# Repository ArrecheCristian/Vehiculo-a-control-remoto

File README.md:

# Vehiculo a control remoto
* Integración de Hardware y Software. 
* Diseño y desarrollo de PCB.
* Integración de componentes de hardware. 
* Manejo y medición de sensor de proximidad.
* Control inalámbrico (vía Bluetooth).
* Batería.
* Lenguaje de programación C.

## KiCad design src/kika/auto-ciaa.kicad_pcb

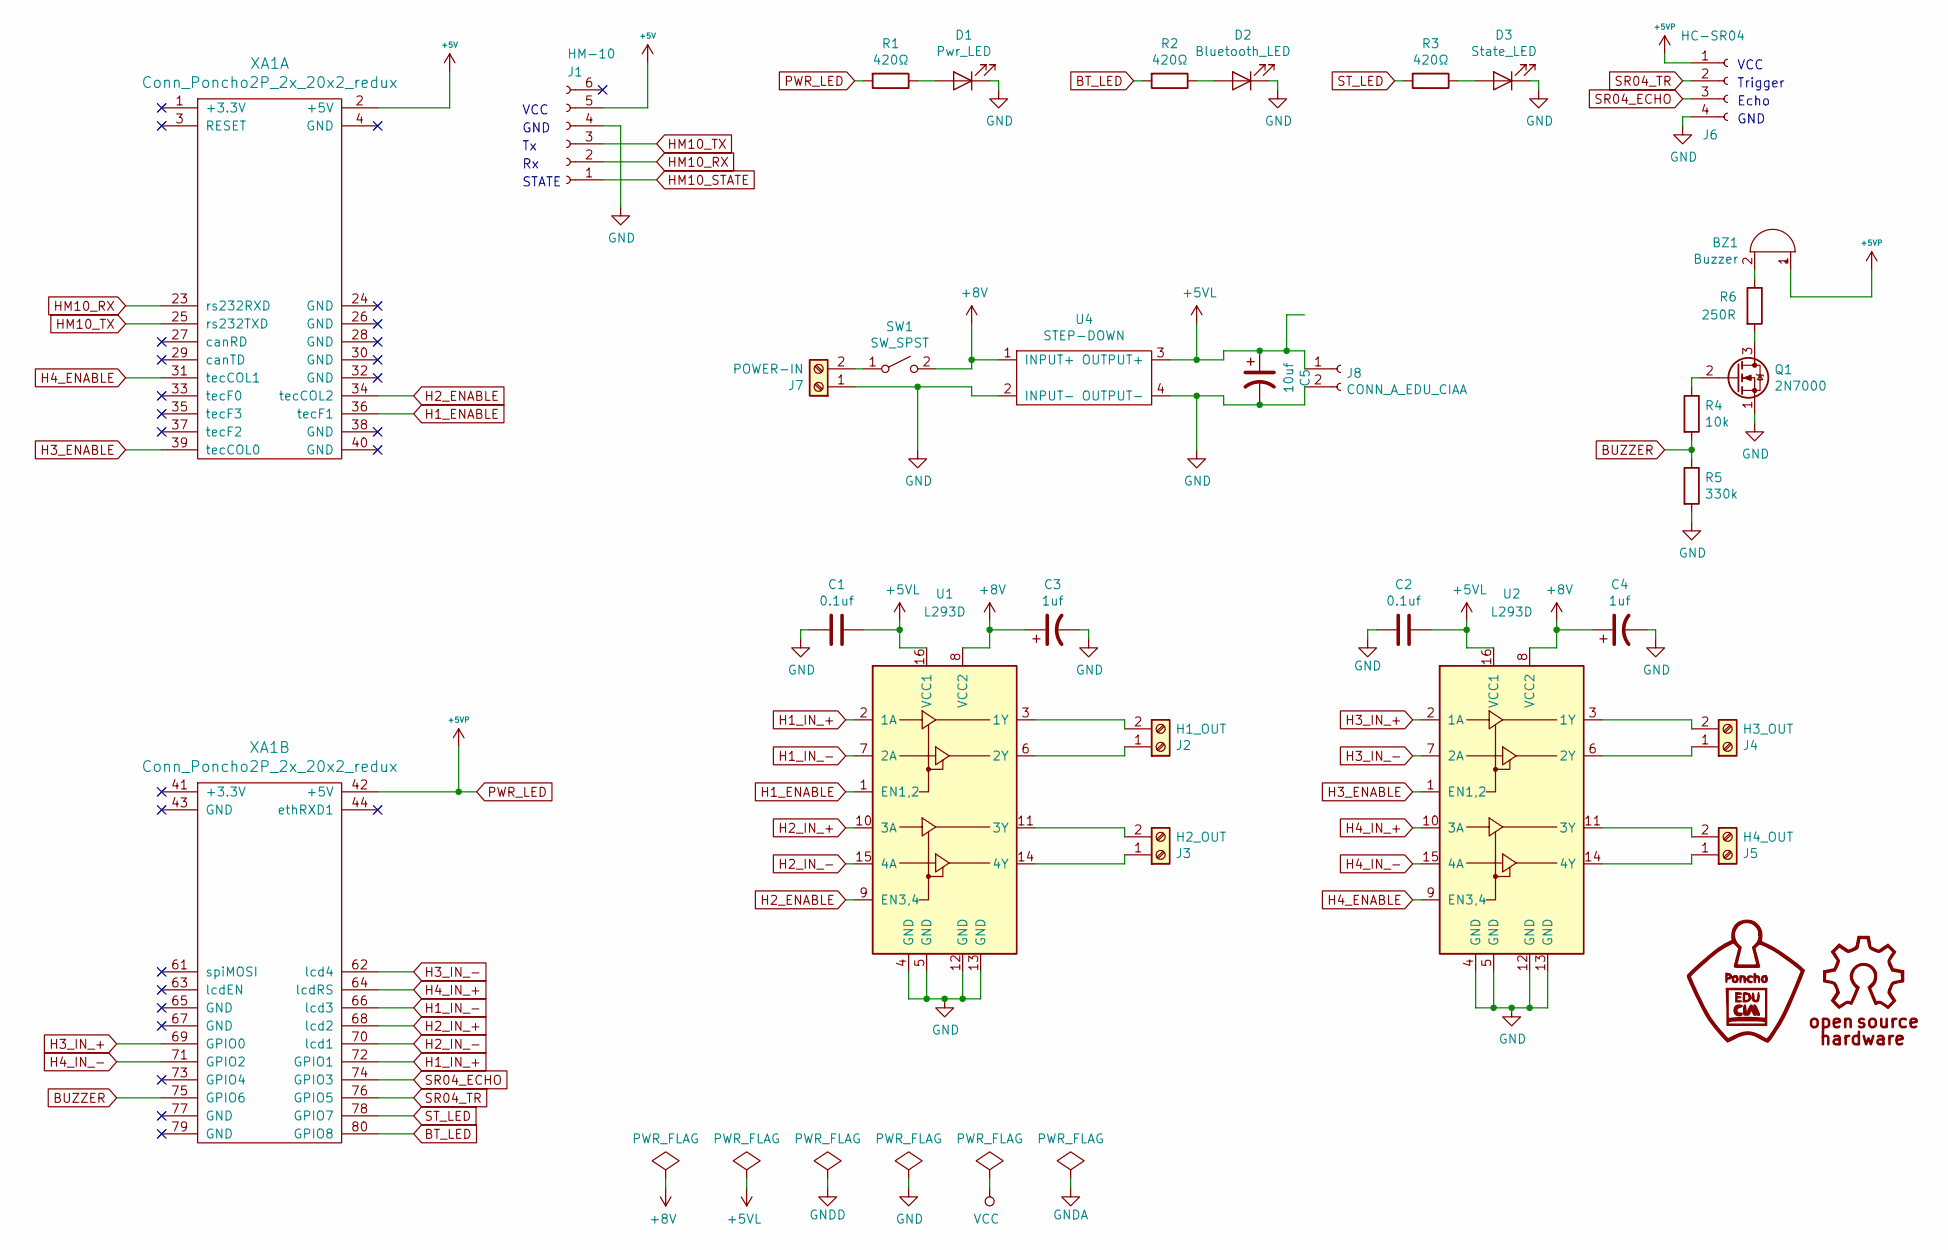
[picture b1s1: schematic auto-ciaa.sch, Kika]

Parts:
BZ1: Buzzer; Buzzer_12x9.5RM7.6
C1, C2: 0.1uf; C_Disc_D4.3mm_W1.9mm_P5.00mm
C3, C4: 1uf; CP_Radial_D5.0mm_P2.50mm
C5: 10uf; CP_Radial_D8.0mm_P2.50mm
D1: Pwr_LED; LED_D5.0mm
D2: Bluetooth_LED; LED_D5.0mm
D3: State_LED; LED_D5.0mm
J1: HM-10; PinSocket_1x06_P2.54mm_Vertical
J2: H1_OUT; TerminalBlock_bornier-2_P5.08mm
J3: H2_OUT; TerminalBlock_bornier-2_P5.08mm
J4: H3_OUT; TerminalBlock_bornier-2_P5.08mm
J5: H4_OUT; TerminalBlock_bornier-2_P5.08mm
J6: HC-SR04; PinSocket_1x04_P2.54mm_Vertical
J7: POWER-IN; TerminalBlock_bornier-2_P5.08mm
J8: CONN_A_EDU_CIAA; Molex_KK-254_AE-6410-02A_1x02_P2.54mm_Vertical
Q1: 2N7000; TO-92_Inline_Wide
R1, R2, R3: 420Ω; R_Axial_DIN0207_L6.3mm_D2.5mm_P7.62mm_Horizontal
R4: 10k; R_Axial_DIN0207_L6.3mm_D2.5mm_P7.62mm_Horizontal
R5: 330k; R_Axial_DIN0207_L6.3mm_D2.5mm_P7.62mm_Horizontal
R6: 250R; R_Axial_DIN0207_L6.3mm_D2.5mm_P7.62mm_Horizontal
SW1: SW_SPST; SW_DIP_SPSTx01_Slide_9.78x4.72mm_W7.62mm_P2.54mm
U1, U2: L293D; DIP-16_W7.62mm
U4: STEP-DOWN; mini360
XA1: Conn_Poncho2P_2x_20x2_redux; Conn_Poncho_SinBorde

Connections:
+5V: J1.5, XA1.2 (+5V)
+5VL: C1.1, C2.1, C5.1, J8.1, U1.16 (VCC1), U2.16 (VCC1), U4.3 (OUTPUT+)
+8V: C3.1, C4.1, SW1.2 (B), U1.8 (VCC2), U2.8 (VCC2), U4.1 (INPUT+)
BT_LED: R2.2, XA1.80 (GPIO8)
BUZZER: R4.2, R5.1, XA1.75 (GPIO6)
GND: C1.2, C2.2, C3.2, C4.2, C5.2, D1.1 (K), D2.1 (K), D3.1 (K), J1.4, J6.4, J7.1, J8.2, Q1.1 (S), R5.2, U1.4 (GND), U1.5 (GND), U1.12 (GND), U1.13 (GND), U2.4 (GND), U2.5 (GND), U2.12 (GND), U2.13 (GND), U4.2 (INPUT-), U4.4 (OUTPUT-)
H1_ENABLE: U1.1 (EN1,2), XA1.36 (tecF1)
H1_IN_+: U1.2 (1A), XA1.72 (GPIO1)
H1_IN_-: U1.7 (2A), XA1.66 (lcd3)
H2_ENABLE: U1.9 (EN3,4), XA1.34 (tecCOL2)
H2_IN_+: U1.10 (3A), XA1.68 (lcd2)
H2_IN_-: U1.15 (4A), XA1.70 (lcd1)
H3_ENABLE: U2.1 (EN1,2), XA1.39 (tecCOL0)
H3_IN_+: U2.2 (1A), XA1.69 (GPIO0)
H3_IN_-: U2.7 (2A), XA1.62 (lcd4)
H4_ENABLE: U2.9 (EN3,4), XA1.31 (tecCOL1)
H4_IN_+: U2.10 (3A), XA1.64 (lcdRS)
H4_IN_-: U2.15 (4A), XA1.71 (GPIO2)
HM10_RX: J1.2, XA1.23 (rs232RXD)
HM10_TX: J1.3, XA1.25 (rs232TXD)
unnamed: BZ1.2 (+), R6.1
unnamed: D1.2 (A), R1.1
unnamed: D2.2 (A), R2.1
unnamed: D3.2 (A), R3.1
unnamed: J2.1, U1.6 (2Y)
unnamed: J2.2, U1.3 (1Y)
unnamed: J3.1, U1.14 (4Y)
unnamed: J3.2, U1.11 (3Y)
unnamed: J4.1, U2.6 (2Y)
unnamed: J4.2, U2.3 (1Y)
unnamed: J5.1, U2.14 (4Y)
unnamed: J5.2, U2.11 (3Y)
unnamed: J7.2, SW1.1 (A)
unnamed: Q1.2 (G), R4.1
unnamed: Q1.3 (D), R6.2
PWR_LED: BZ1.1 (-), J6.1, R1.2, XA1.42 (+5V)
SR04_ECHO: J6.3, XA1.74 (GPIO3)
SR04_TR: J6.2, XA1.76 (GPIO5)
ST_LED: R3.2, XA1.78 (GPIO7)

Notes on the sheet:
VCC
Trigger
Echo
GND
STATE

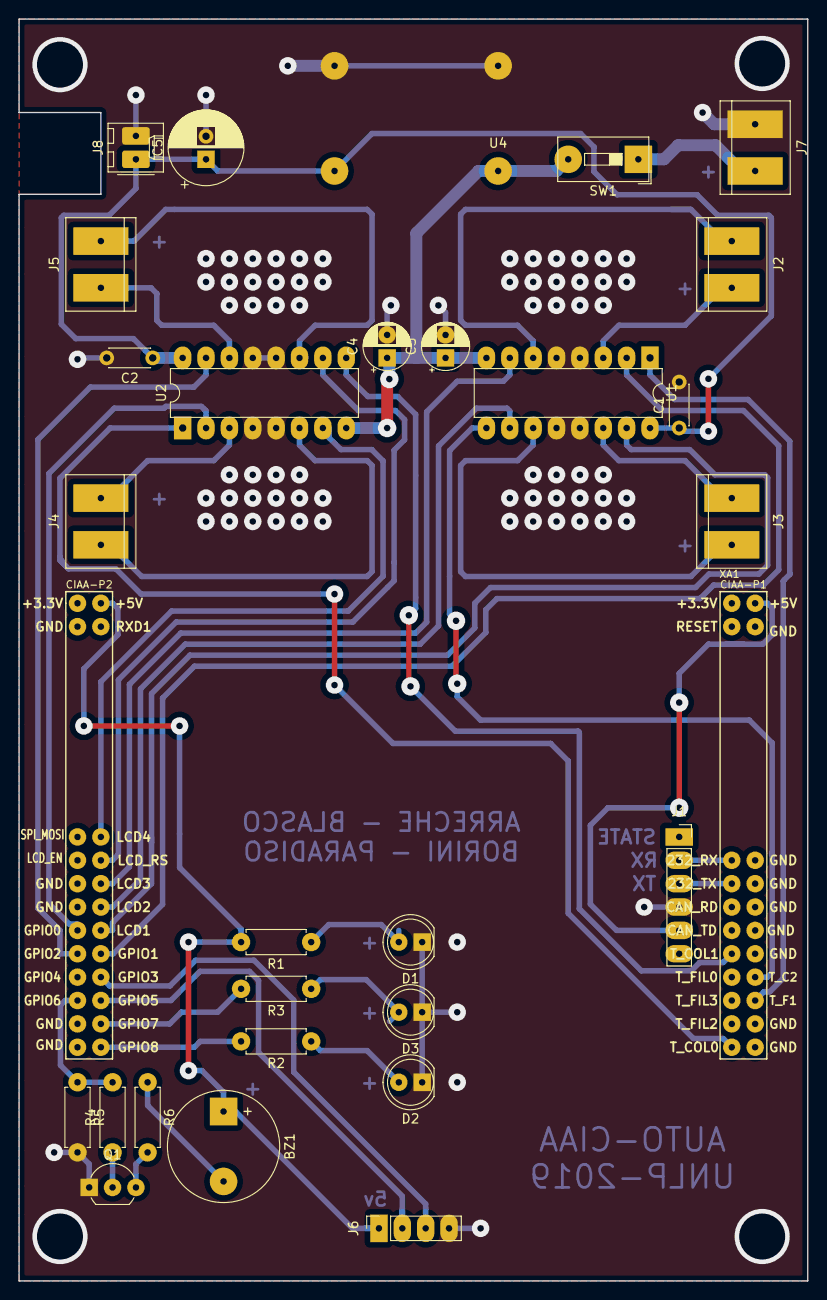
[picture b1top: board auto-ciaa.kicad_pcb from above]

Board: 2 copper layers, 85.7 x 137.2 mm, 29 parts (0 on the bottom side), 39 nets.

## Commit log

2021-02-08 Proyecto final
    Subida del proyecto a Git.
